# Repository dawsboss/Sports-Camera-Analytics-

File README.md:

# Sideline

A pipeline that turns match footage into per-player data a coach can use.
It is built for a fixed camera that sees the whole pitch; Veo follow-cam
exports are the proof-of-concept input, used because the footage already
exists and because a hostile input keeps the pipeline honest. The two
differ in exactly one stage, registration, and everything else is shared.
The design is in [`docs/SPEC.md`](docs/SPEC.md); read it first.

Published aggregates land in Firebase next to the fixture that
[`soccer-manager`](https://github.com/dawsboss/soccer-manager-) already
tracks. Raw video never leaves the homelab.

## Where this is

| Milestone | State |
| --- | --- |
| M1 registration spike | **Run on two real Veo exports. The classical detector fails the gate on both** after every improvement that could be measured (per-frame grass colour, line thresholds that follow it, plausibility checks compared three ways on four datasets). A pretrained line network, unmodified, already finds on the worn field what the classical code cannot; fine-tuning it on this footage is the next registrar. The measurements are in [`spike/evals/`](spike/evals/) and the plan in [`docs/NEXT.md`](docs/NEXT.md). |
| M2 skeleton | API, Postgres, MinIO, RQ worker, S0 ingest and S1 sampling. Runs with no services on a laptop, or under `docker compose`. |
| M3 detection | Feasibility measured: players are found off the shelf, the ball is not, by any model tried. A ball detector trained on this footage is the gate for possession, passes and restarts. Not built. |
| M4 onward | Not started. |

## Run the M1 spike

```
python -m venv .venv && . .venv/bin/activate
pip install -e ".[dev]"
sideline spike path/to/veo-export.mp4 --frames 200 --out spike/out
```

Then open `spike/out/overlays/` and read the summary. [`spike/README.md`](spike/README.md)
says what the numbers mean, what the overlays show, and what the machinery
cannot do yet. `sideline spike --selftest` runs the same thing on rendered
frames with known truth, which checks the code rather than the footage.

## Run the skeleton

With no services at all, against a directory and SQLite:

```
sideline ingest path/to/match.mp4 --pitch-length 100 --pitch-width 64
ls data/blobs/matches/<id>/
```

With the real stack:

```
docker compose up --build
curl -F file=@match.mp4 -F capture_mode=followcam -F pitch_length=100 -F pitch_width=64 \
     -F kickoff_offset_ms=95000 localhost:8000/matches
```

The API docs are at `localhost:8000/docs`, MinIO's console at `:9001`. The
upload takes the accompanying inputs the spec lists (`sm_match_id`, roster,
stints and periods as JSON, kickoff offset, pitch dimensions), stores the
file under `matches/{id}/source/`, and queues S0 then S1 unless `stages`
names more. Every stage writes `matches/{id}/{stage}/v{n}/` with a
`manifest.json` recording its config and inputs; a re-run is a new version.

Players, the ball and restarts, on a machine with a GPU and the `eval`
extra installed, with no services:

```
sideline ingest match.mp4 --kickoff-offset-ms 83000 \
    --stages s0_ingest,s1_sampling,s2_detection,s3_tracking,s8_events
python spike/evals/restarts_on_taps.py --match-dir data/blobs/matches/<id> --sm matches-node.json
```

The first writes `detections.parquet`, `fragments.parquet` and
`events.parquet` (throw-ins, corners, goal kicks, free kicks, kick-offs,
keeper claims, each with the taker's track), plus `events.csv`, the same
rows as a coach would write them down: match clock, event, who, how sure.
`sideline log <id>` prints that list and `sideline overlay <id>` renders
it onto the frames. The eval script scores the events against the
corners, throw-ins and goal kicks the coach tapped in the minutes app.
`docs/NEXT.md`, "Restarts without registration", says why this needs no
pitch coordinates and what it still needs.

## Review, on your own network

```
sideline serve --data ./data          # the same directory `sideline ingest` wrote
```

Then open `http://<that machine>:8000/review` from any browser on the
same network, phone included. The landing page lists the matches with
where each has got to, and takes new film: a video file, or a direct link
to one that the server fetches (a Veo match page is not the file; the
tagger's README says how to get the direct link). Ingest and sampling run
in the background on the machine serving the page, and the list shows how
far each step has got. A Veo export is H.264 already, so ingest copies its
stream into a fresh MP4 in a minute or two rather than re-encoding it for
an hour; anything else is transcoded. Detection needs the model and a GPU,
so by default it is left for the GPU machine:

```
rsync -a sideline@<homelab>:/srv/sideline/data/ ./data/      # bring the match over
sideline run <match id> --data ./data                        # detection, tracking, restarts
rsync -a ./data/blobs/ sideline@<homelab>:/srv/sideline/data/blobs/   # send the artifacts back
```

Tick "also find the players, the ball and the restarts here" to run it
all on the serving machine instead, when that machine has the model.

A match opens into the review. The page plays the match at each
event the pipeline wrote, draws the taker, the ball and every tracked
box, and takes one of four taps: right; what it was instead, one
button or digit per kind; wrong taker, by tapping the right player; not
an event. The clip runs from four seconds before the release to eight
after, and `[` and `]` add five seconds at either end. With a roster uploaded it also
names the taker. The chips above the list narrow it to one kind of
event (every throw-in, every unnamed restart), and `j`/`k` and the tap
that follows a verdict then stay within that kind. After a re-run of
the events the verdicts given on the earlier version are shown on the
new one, dashed, wherever the same moment is still an event; they stay
rows of the version they were given on. Each tap is a row in the database (`event_decisions`,
`review_decisions`), never an edit to an artifact, and
`GET /matches/<id>/review/decisions` exports them. The frames the page
shows are most of the footage at 5 fps and are served by this API to
browsers on this network and nowhere else: keep the API on the LAN or a
Tailscale network, never on the open internet and never behind a public
tunnel (the spec's Cloudflare Tunnel option does not apply to this API).
There is no login. The compose stack serves the same page at
`:8000/review`.

### On the homelab, as a service

On a Debian or Ubuntu machine (a Proxmox LXC or VM), as root:

```
curl -fsSL https://raw.githubusercontent.com/dawsboss/Sports-Camera-Analytics-/main/deploy/install-homelab.sh | bash
```

or clone the repository and run `deploy/install-homelab.sh`. It makes a
`sideline` user, a checkout and a virtualenv under `/srv/sideline`, and a
systemd service (`deploy/sideline.service`) that serves the API and the
review page on port 8000 of every interface, from boot, with uploads
running on a background thread of the service. Run it again to update.
Matches live in `/srv/sideline/data`, the layout `sideline ingest --data`
writes, so a match can also be processed whole on the GPU machine and
copied in:

```
rsync -a --delete ./data/ sideline@<homelab>:/srv/sideline/data/
```

Review on the homelab's copy from then on; the verdicts are rows in its
database. `SIDELINE_BRANCH=<branch>` before the script installs a branch
instead of `main`.

### The GPU worker

With a GPU in the container, the same machine does the detection too and
the gaming PC drops out of the loop. Run the installer with
`SIDELINE_GPU=1`. It installs torch from the CUDA 12.6 wheels (the last to
support a Pascal card such as a GTX 1080; set `SIDELINE_TORCH_INDEX` for a
newer card), the detector, and a second service, `sideline-worker`, which
polls the database for queued jobs and runs them in its own process while
the API only queues them. The worker holds the detector and the GPU; the
API stays light. Tick "also find the players, the ball and the restarts
here" when adding film, and the list shows detection running frame by
frame.

The container needs the card first. Share it at the host rather than
passing it through: install the NVIDIA driver on the Proxmox host, then hand
the devices to the container (`/dev/nvidia0`, `/dev/nvidiactl`,
`/dev/nvidia-uvm`, `/dev/nvidia-uvm-tools`, `/dev/nvidia-modeset` as
present, as `dev0:`.. entries on the container, or the older
`lxc.cgroup2.devices.allow` and `lxc.mount.entry` lines) and install the
same driver version's user-space libraries inside it. Any other container
can mount the same devices and share the card; the driver time-slices it,
and the eight gigabytes of memory are what they contend for. If another
project needs the card by day, a systemd timer that starts
`sideline-worker` at night is the whole scheduling policy.

## Layout

```
sideline/
  contracts.py        tracks/events/registration Parquet schemas, match.json, player_stats.json
  timeline.py         video time <-> match seconds, and the minutes app's taps, via soccer-manager's nodes
  sports/             the plugin boundary; soccer.py is the pitch model, entities, stat definitions, restart rules
  detection.py        S2's detector behind a protocol: an Ultralytics checkpoint, or a script for tests
  tracking.py         S3's tracker: people by overlap or centre, the ball by where it went, no dependencies
  events.py           dead balls from fragments: still, then struck or thrown, and who took it, in player heights
  possession.py       who has the ball in each sample: feet or hands within a touch, spells that survive a missed sample
  registration/       S5: one interface, two implementations
    followcam.py        per-frame fit from painted lines (the PoC)
    static.py           clicked landmarks once per placement, homography or spline (the product)
    lines.py            grass, paint, line segments
    synthetic.py        frames rendered through a known camera, for tests and the selftest
  storage/            blob store (local or MinIO) and the versioned artifact layout
  db/                 matches, jobs, stage runs, review decisions
  stages/             s0_ingest, s1_sampling, s2_detection, s3_tracking, s8_events
  overlay.py          the sampled frames with tracks, the ball's path and each event's call, as an MP4
  api/                FastAPI: uploads, artifacts, and the review page's routes
  worker/             RQ worker
  spike.py, cli.py    the M1 spike and the `sideline` command
deploy/               install-homelab.sh and sideline.service: the API as a LAN service on the homelab
docs/SPEC.md          the design, copied from the living doc
web/                  the tagger (GitHub Pages) and review.html (served by the API on your network)
hardware/             the static rig (M9): what to buy, the printed four-camera head or hidden pod, aim cards
tests/                pytest; everything runs on a CPU with no services
```

## Tests

```
pytest
```

Registration is checked against frames rendered through a known camera:
box views must land within a metre of the truth, a midfield view with one
crossing line must be refused with a reason, and a sweep of views must
register at least 70% with few confident wrong answers. The stages, the
API and the local pipeline run on a three-second synthetic clip. None of
that is the M1 gate; the gate is real footage.

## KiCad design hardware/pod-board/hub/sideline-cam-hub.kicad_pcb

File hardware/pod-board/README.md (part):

# The pod board: our own cameras instead of the IP domes

Four small Sony IMX678 camera heads in one sealed pod. An RK3588
module in the pod records all four 4K streams to an SSD, and one PoE++
cable runs down the mast. It replaces the IP cameras that the Sideline
Rig Brief (the rig's design doc of 25 September 2026) picks in Part 1,
two Reolink RLC-843A domes and two RLC-820A turrets, and shrinks the
brief's Part 3 pod around them. Against the rigs in `../README.md`, it
replaces the cameras, the switch and the recorder.

It is built from one open-hardware carrier and one new board:

- **The carrier** is [Antmicro's Jetson Orin
  Baseboard](https://github.com/antmicro/jetson-orin-baseboard). It is
  built as it is, with one resistor array moved, and it carries a
  [Mixtile Core 3588E](https://www.mixtile.com/core-3588e/) (RK3588).
- **The camera hub** (`hub/`) is the new PCB. It turns the baseboard's
  two 50-pin camera connectors into four Raspberry Pi 5 style camera
  ports. It adds a power switch per camera, a frame-sync bus that makes
  one camera the master, an IMU that samples on the frame pulse and a
  humidity sensor.

**State:** designed and checked in KiCad, and nothing bought, built or
filmed. The hub's schematic passes ERC, and its board passes DRC and
the schematic-parity check (see "The camera hub"). Every figure below
is either sourced or marked as an estimate.

## Why build it: smaller, lighter, and our settings

| | Recommended IP set (brief, Part 1) | Pod board |
| --- | --- | --- |
| Cameras on the mast | 2.44 kg | about 0.1 kg: four heads with lenses (estimate) |
| Whole rig on the mast | about 4.4 kg of a 4.5 kg rating | about 0.9 kg (estimate, see "Power, data, heat and weight") |
| Pod | about 300 x 240 x 300 mm (design v2) | about 160 x 140 x 120 mm (estimate; not drawn yet) |
| Bitrate per camera | 8 Mbps, the camera's maximum | our choice; plan 35 Mbps, test 20 to 50 |
| Shutter | "manual", fastest step not published | set in the sensor: 1/1000 s |
| White balance | whatever the firmware allows | fixed ISP gains for the match |
| Lens | motorized zoom that must return after power-up | fixed M12 lenses, focus locked |
| Frame sync | none | one XVS/XHS pulse drives all four sensors |
| Mast tilt | not measured | an IMU sample tagged to every frame |
| Smallest ball, 11v11 | 9.2 px | 8.0 px (middle of the near goal line) |
| Ball at the far corner | 9.7 px | 10.1 px |
| Cost of the first unit | $500 | roughly $1,300 to $2,200 (estimate, see "What to buy") |

The bitrate decides it, as the brief says. An 8 Mbps stream is the
first thing to smear a 9 px ball; here it is a setting.

## What it sees

`rig_geometry.py --head homebrew-678` models the heads: IMX678 at
3840 x 2160, with Commonlands M12 lenses modelled rectilinear. The
lens angles are Commonlands' own figures for each lens on the IMX678.
The rig is an 8 m mast, 10 m behind the touchline, at halfway:

| | 11v11 (100 x 64 m) | 9v9 (69 x 46 m) | 7v7 (55 x 37 m) |
| --- | --- | --- | --- |
| Smallest ball anywhere | 8.0 px | 10.4 px | 12.7 px |
| Ball at the far corner | 10.1 px | 12.6 px | 15.2 px |
| Smallest player | 61 px | 70 px | 85 px |
| Worst foot position | 0.25 m per px | 0.13 | 0.09 |
| Pitch + 2 m in frame, feet and heads | 100% | 100% | 100% |
| Trials with a gap inside the lines, every camera up to 2 degrees off | 0 of 300 | 0 of 300 | 0 of 300 |

| Camera | Lens | Horizontal angle on IMX678 | Yaw, L / R | Tilt down |
| --- | --- | --- | --- | --- |
| FAR-L, FAR-R | [Commonlands CIL083](https://commonlands.com/products/low-distortion-8mm-m12-lenses), 8.0 mm f/2.8, -0.5% TV distortion | 51 degrees | -24 / +24 | 4 |
| NEAR-L, NEAR-R | [Commonlands CIL042](https://commonlands.com/products/no-distortion-4mm-m12-lens-cil042), 4.2 mm f/2.6, -0.7% TV distortion | 85 degrees | -40 / +40 | 29 |

Aim cards and coverage maps for all three pitches are in `aim/`.

- **Why these aims.** A wider far pair (around 32 degrees of yaw) gets
  the smallest ball up to 9.3 px. But it leaves the middle of the far
  touchline to the near cameras' top edge, and 7 to 27% of the 2-degree
  trials then lose it. The far pair turns in to overlap there instead.
- **Where it gives up to the Reolinks.** Only the middle of each goal
  line, near side, falls below 9 px: 0.9% of the pitch. The Reolinks'
  near lens is a barrel-distorted security lens, which puts more pixels
  in the middle of the frame than a low-distortion one. A barrel M12
  lens of about 86 degrees would close the gap, but none with a
  published IMX678 angle turned up.
- **What was tried.** Nothing in Commonlands' IMX678 list sits at the
  brief's 56 degrees. The 6.2 mm CIL062 (64 degrees) gives 7.9 px;
  8.0 px is the best of the real lens pairs tried.

## What to buy

Prices were checked on 26 September 2026 where a source is linked, and
the rest are estimates marked "about". Check before ordering.

### Compute and carrier

| Qty | Item | Price | Notes |
| --- | --- | --- | --- |
| 1 | [Antmicro Jetson Orin Baseboard](https://order.openhardware.antmicro.com/), rev 1.3.4 | $499, out of stock at CircuitHub | Or build it from the open files; see "Baseboard setup" for the one change |
| 1 | [Mixtile Core 3588E](https://www.mixtile.com/store/som/core-3588e/), RK3588, 16 GB / 128 GB | between $132 (4 GB / 32 GB) and $338 (32 GB / 256 GB) | Jetson SO-DIMM module on 5 V; the 4 GB version should record, 16 GB leaves room |
| 1 | NVMe SSD, M.2 key M, 1 TB | about $80-150 | Recording; the baseboard's M.2 slot |
| 1 each | A second baseboard, module and SSD (fallback only) | see "If one module is not enough" | Only if the bench test fails; the hub splits between two boards as built |

### Camera heads

| Qty | Item | Price | Notes |
| --- | --- | --- | --- |
| 4 | IMX678 camera board with a Raspberry Pi 22-pin connector and an M12 mount, e.g. [Soho Enterprise SE-SB03-IMX678](https://forums.raspberrypi.com/viewtopic.php?t=306964&start=50) | on request | It must bring out XVS and XHS for sync. Soho's boards sync "by XVS"; confirm XHS before ordering |
| 2 | [Commonlands CIL083](https://commonlands.com/products/low-distortion-8mm-m12-lenses), 650 nm IR-cut | $19 each | Far pair |
| 2 | [Commonlands CIL042](https://commonlands.com/products/no-distortion-4mm-m12-lens-cil042), F/2.6, 650 nm IR-cut | $49 each | Near pair; the F/2.6 version resolves 8 MP at 2 um |

[StarlightEye](https://github.com/will127534/StarlightEye) (IMX585,
C-mount) is the open-source alternative. It has twice the pixel area
for dull days, and brings XVS and XHS out on U.FL. It also needs
C-mount lenses of about 12 mm and 6 mm, which weigh several times the
M12s. The hub serves either.

### The hub and cables

| Qty | Item | Price | Notes |
| --- | --- | --- | --- |
| 1 | Camera hub, this board, 4 layers, assembled one side | about $30-50 each in fives (estimate) | `hub/fab/` has the Gerbers, drill, BOM and placement files |
| 2 | 50-pin 0.5 mm FFC, 100-150 mm | a few dollars | Baseboard J7 to hub J1, J8 to J2; pin N to pin N (see "Cables") |
| 4 | 22-pin 0.5 mm FFC (Raspberry Pi 5 camera cable), 150-200 mm | about $3-5 each | Hub P1-P4 to the heads |
| 4 | JST SH 4-pin leads, 150 mm | about $1 each | Sync, hub J4-J7 to each head's XVS/XHS |

### Base station changes (fixed install on PoE only)

A battery pod needs no base case. This is for a pod on PoE.

| Qty | Item | Notes |
| --- | --- | --- |
| 1 | IEEE 802.3bt PoE++ injector, 60 W, e.g. [TP-Link TL-POE170S](https://www.omadanetworks.com/us/business-networking/omada-accessory-poe-adapter/poe170s/), about $50 | Replaces the USW-Flex and the POE-50-60W injector. The baseboard's PD is 802.3bt (TPS2372-3) |

The travel router, mini PC, power station, mast, guys and Cat6 run are
unchanged from `../README.md`. The four camera patch cables and the
switch go, and the mini PC now only previews, serves time and takes
the offload.

### Battery parts (to price once the power board is designed)

| Qty | Item | Notes |
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
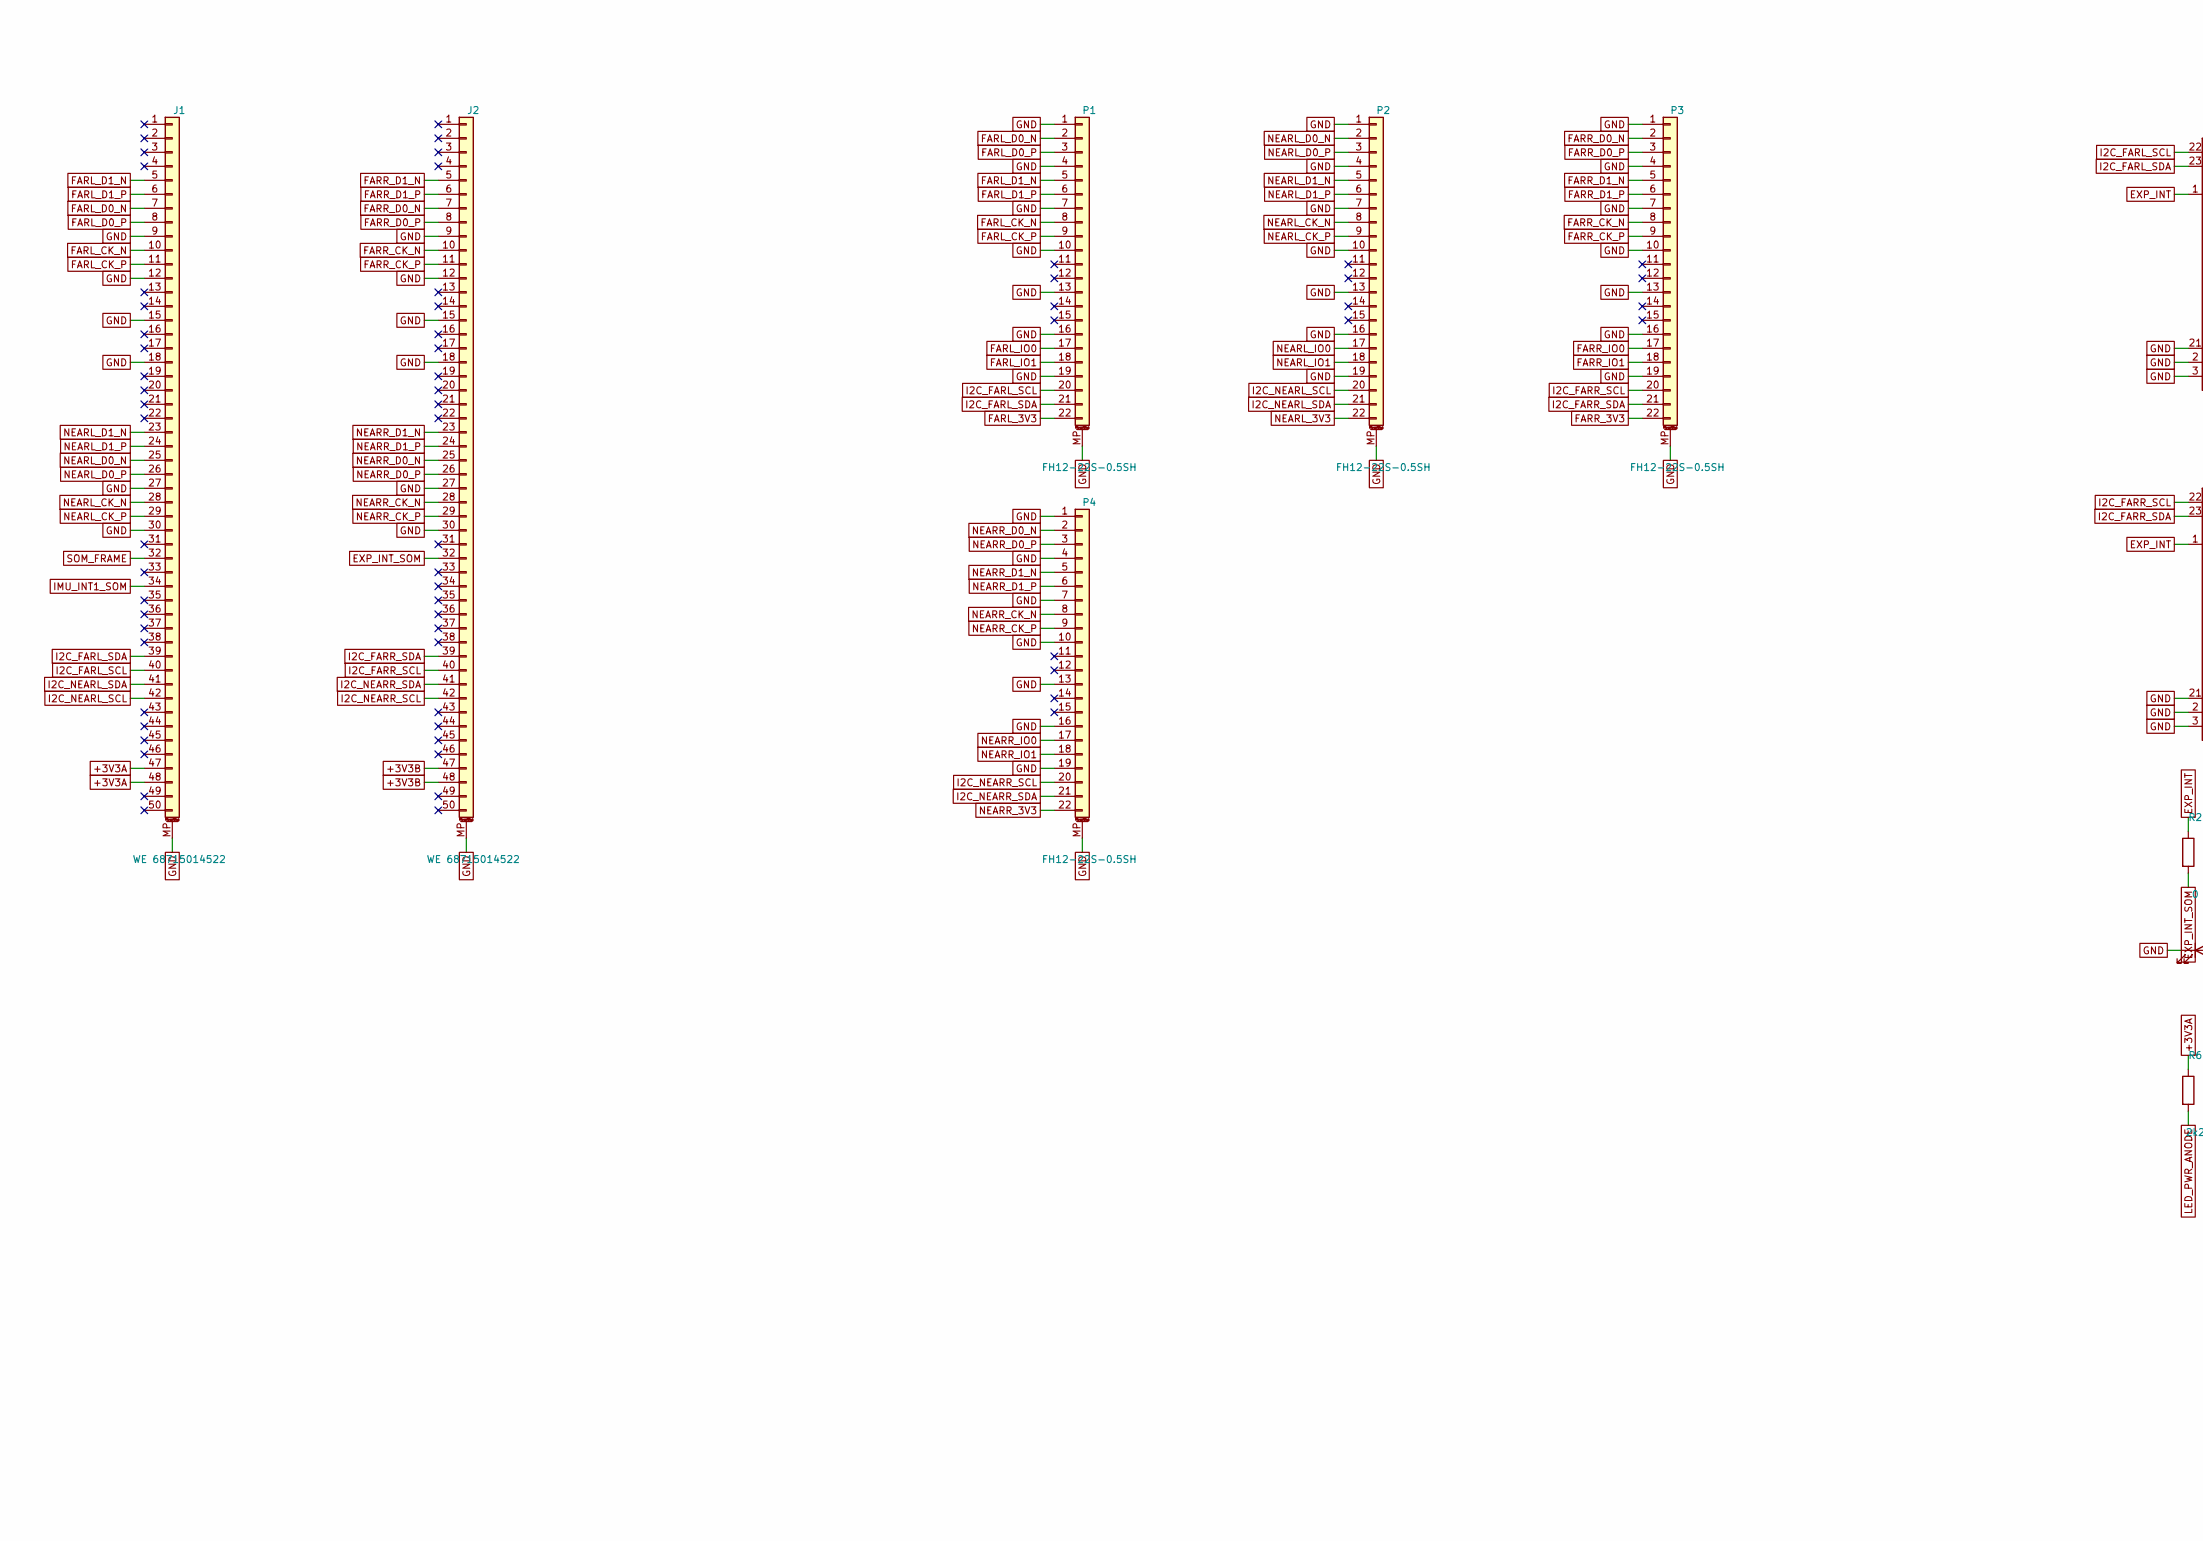
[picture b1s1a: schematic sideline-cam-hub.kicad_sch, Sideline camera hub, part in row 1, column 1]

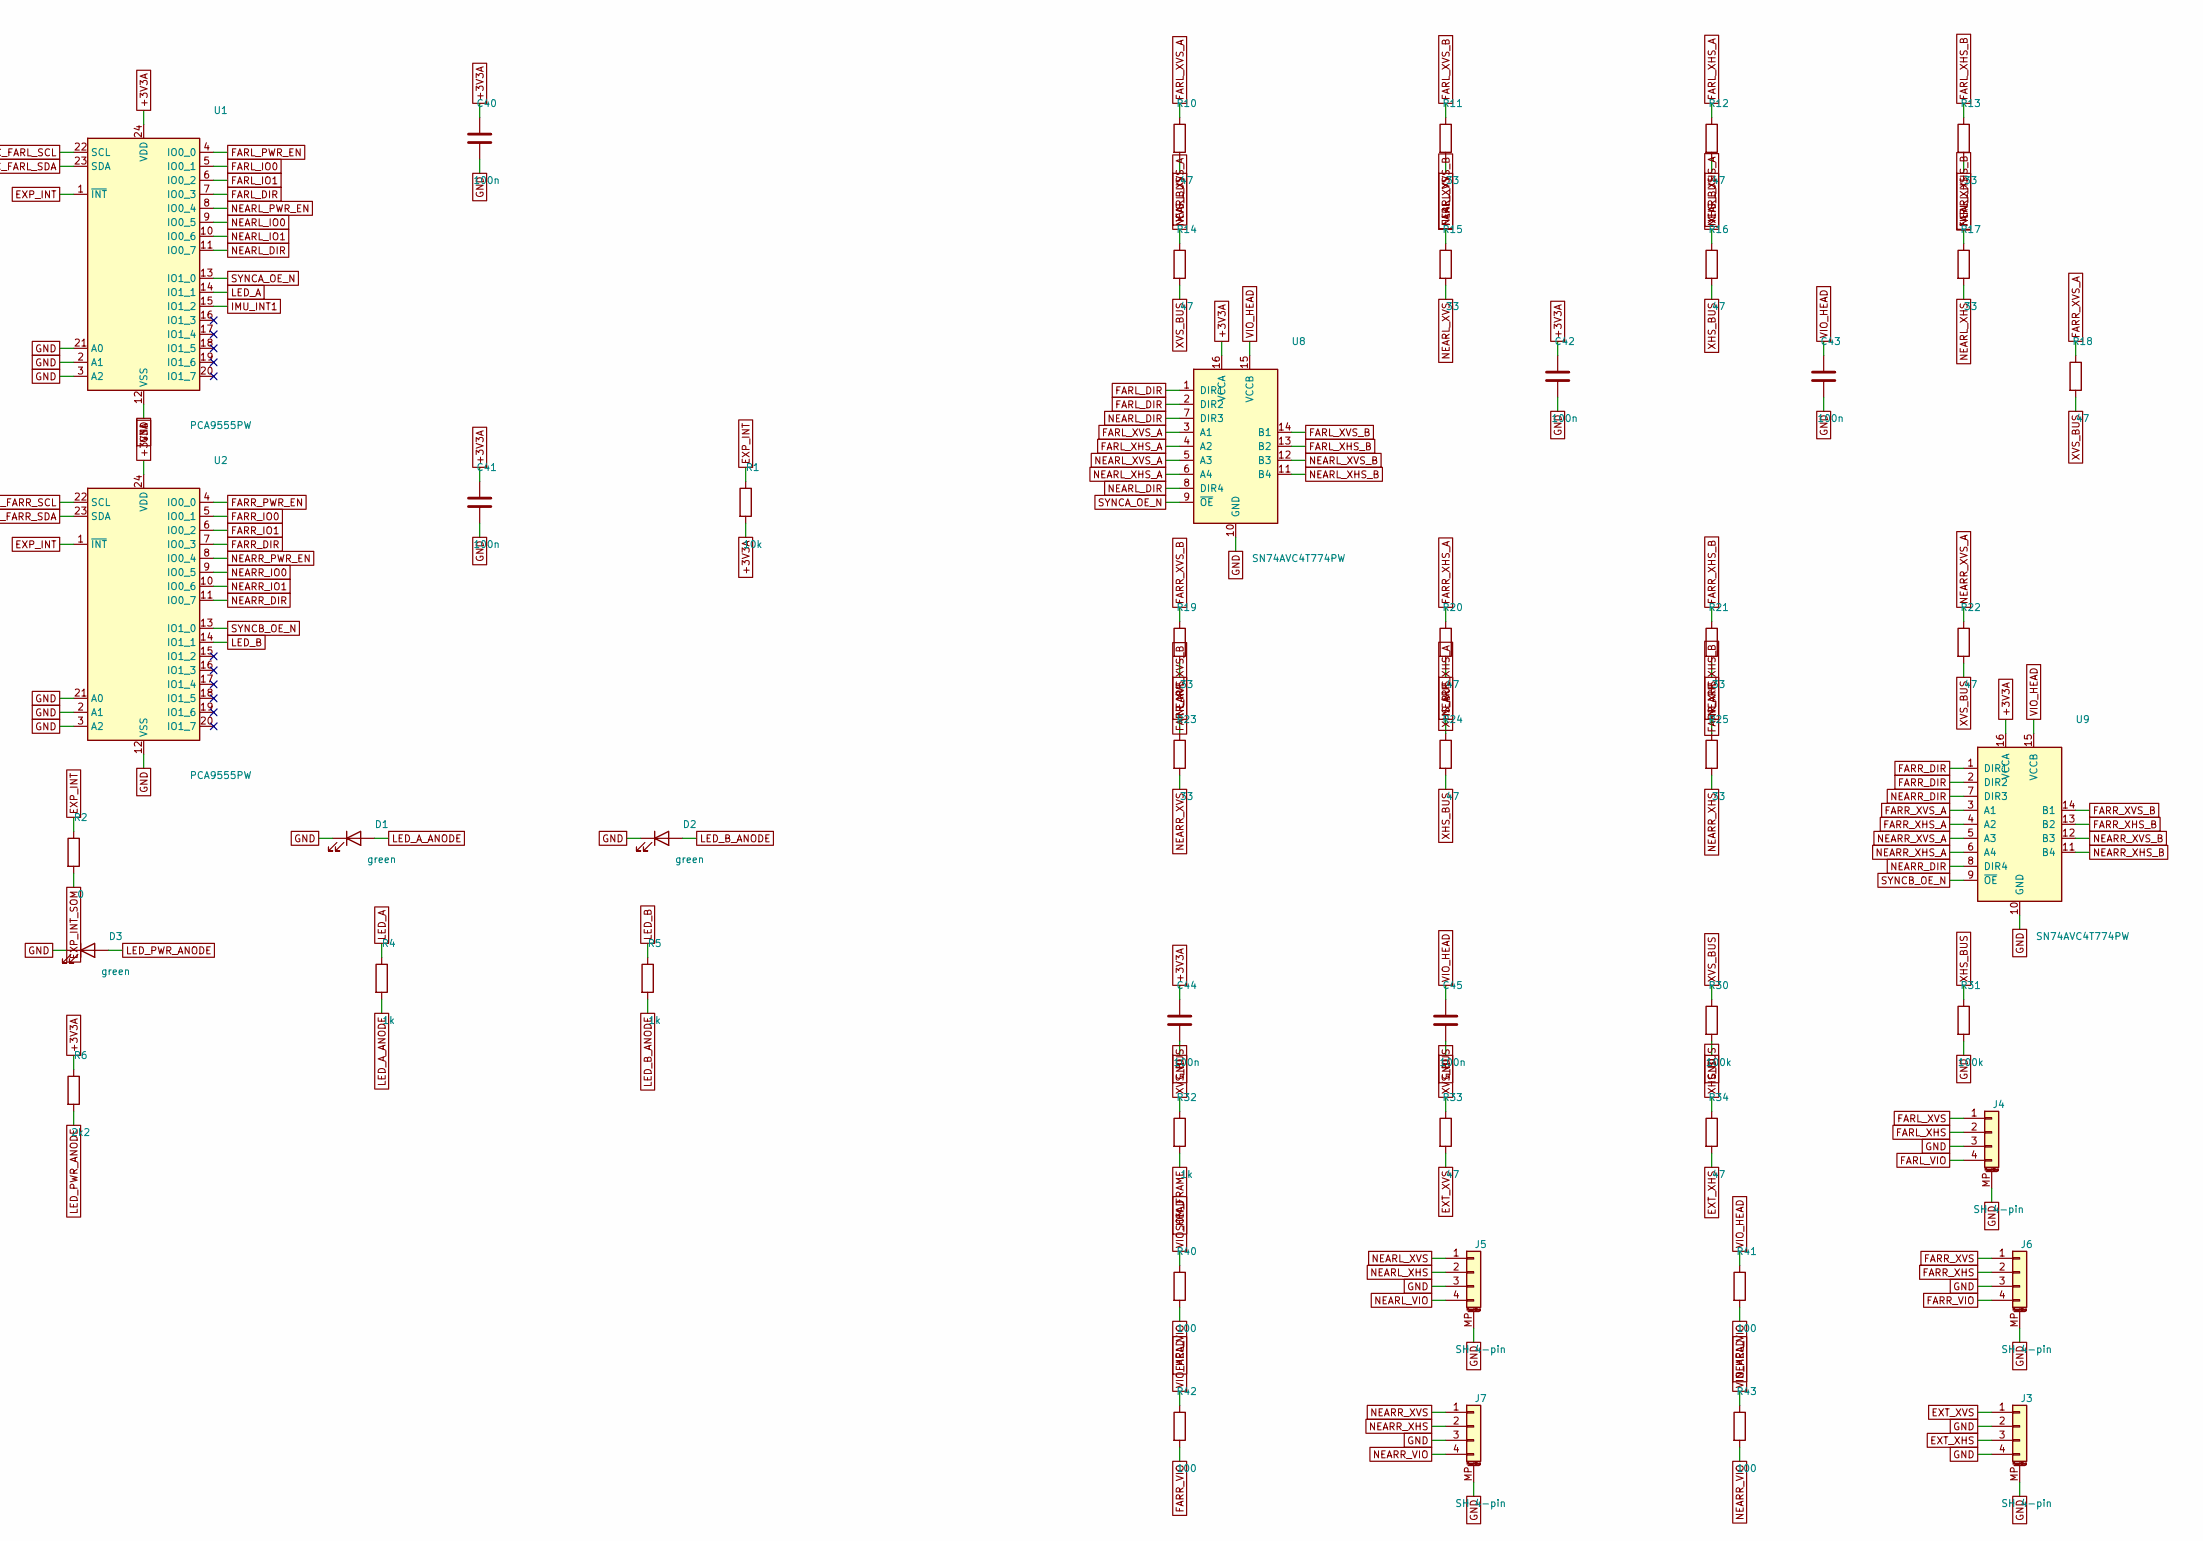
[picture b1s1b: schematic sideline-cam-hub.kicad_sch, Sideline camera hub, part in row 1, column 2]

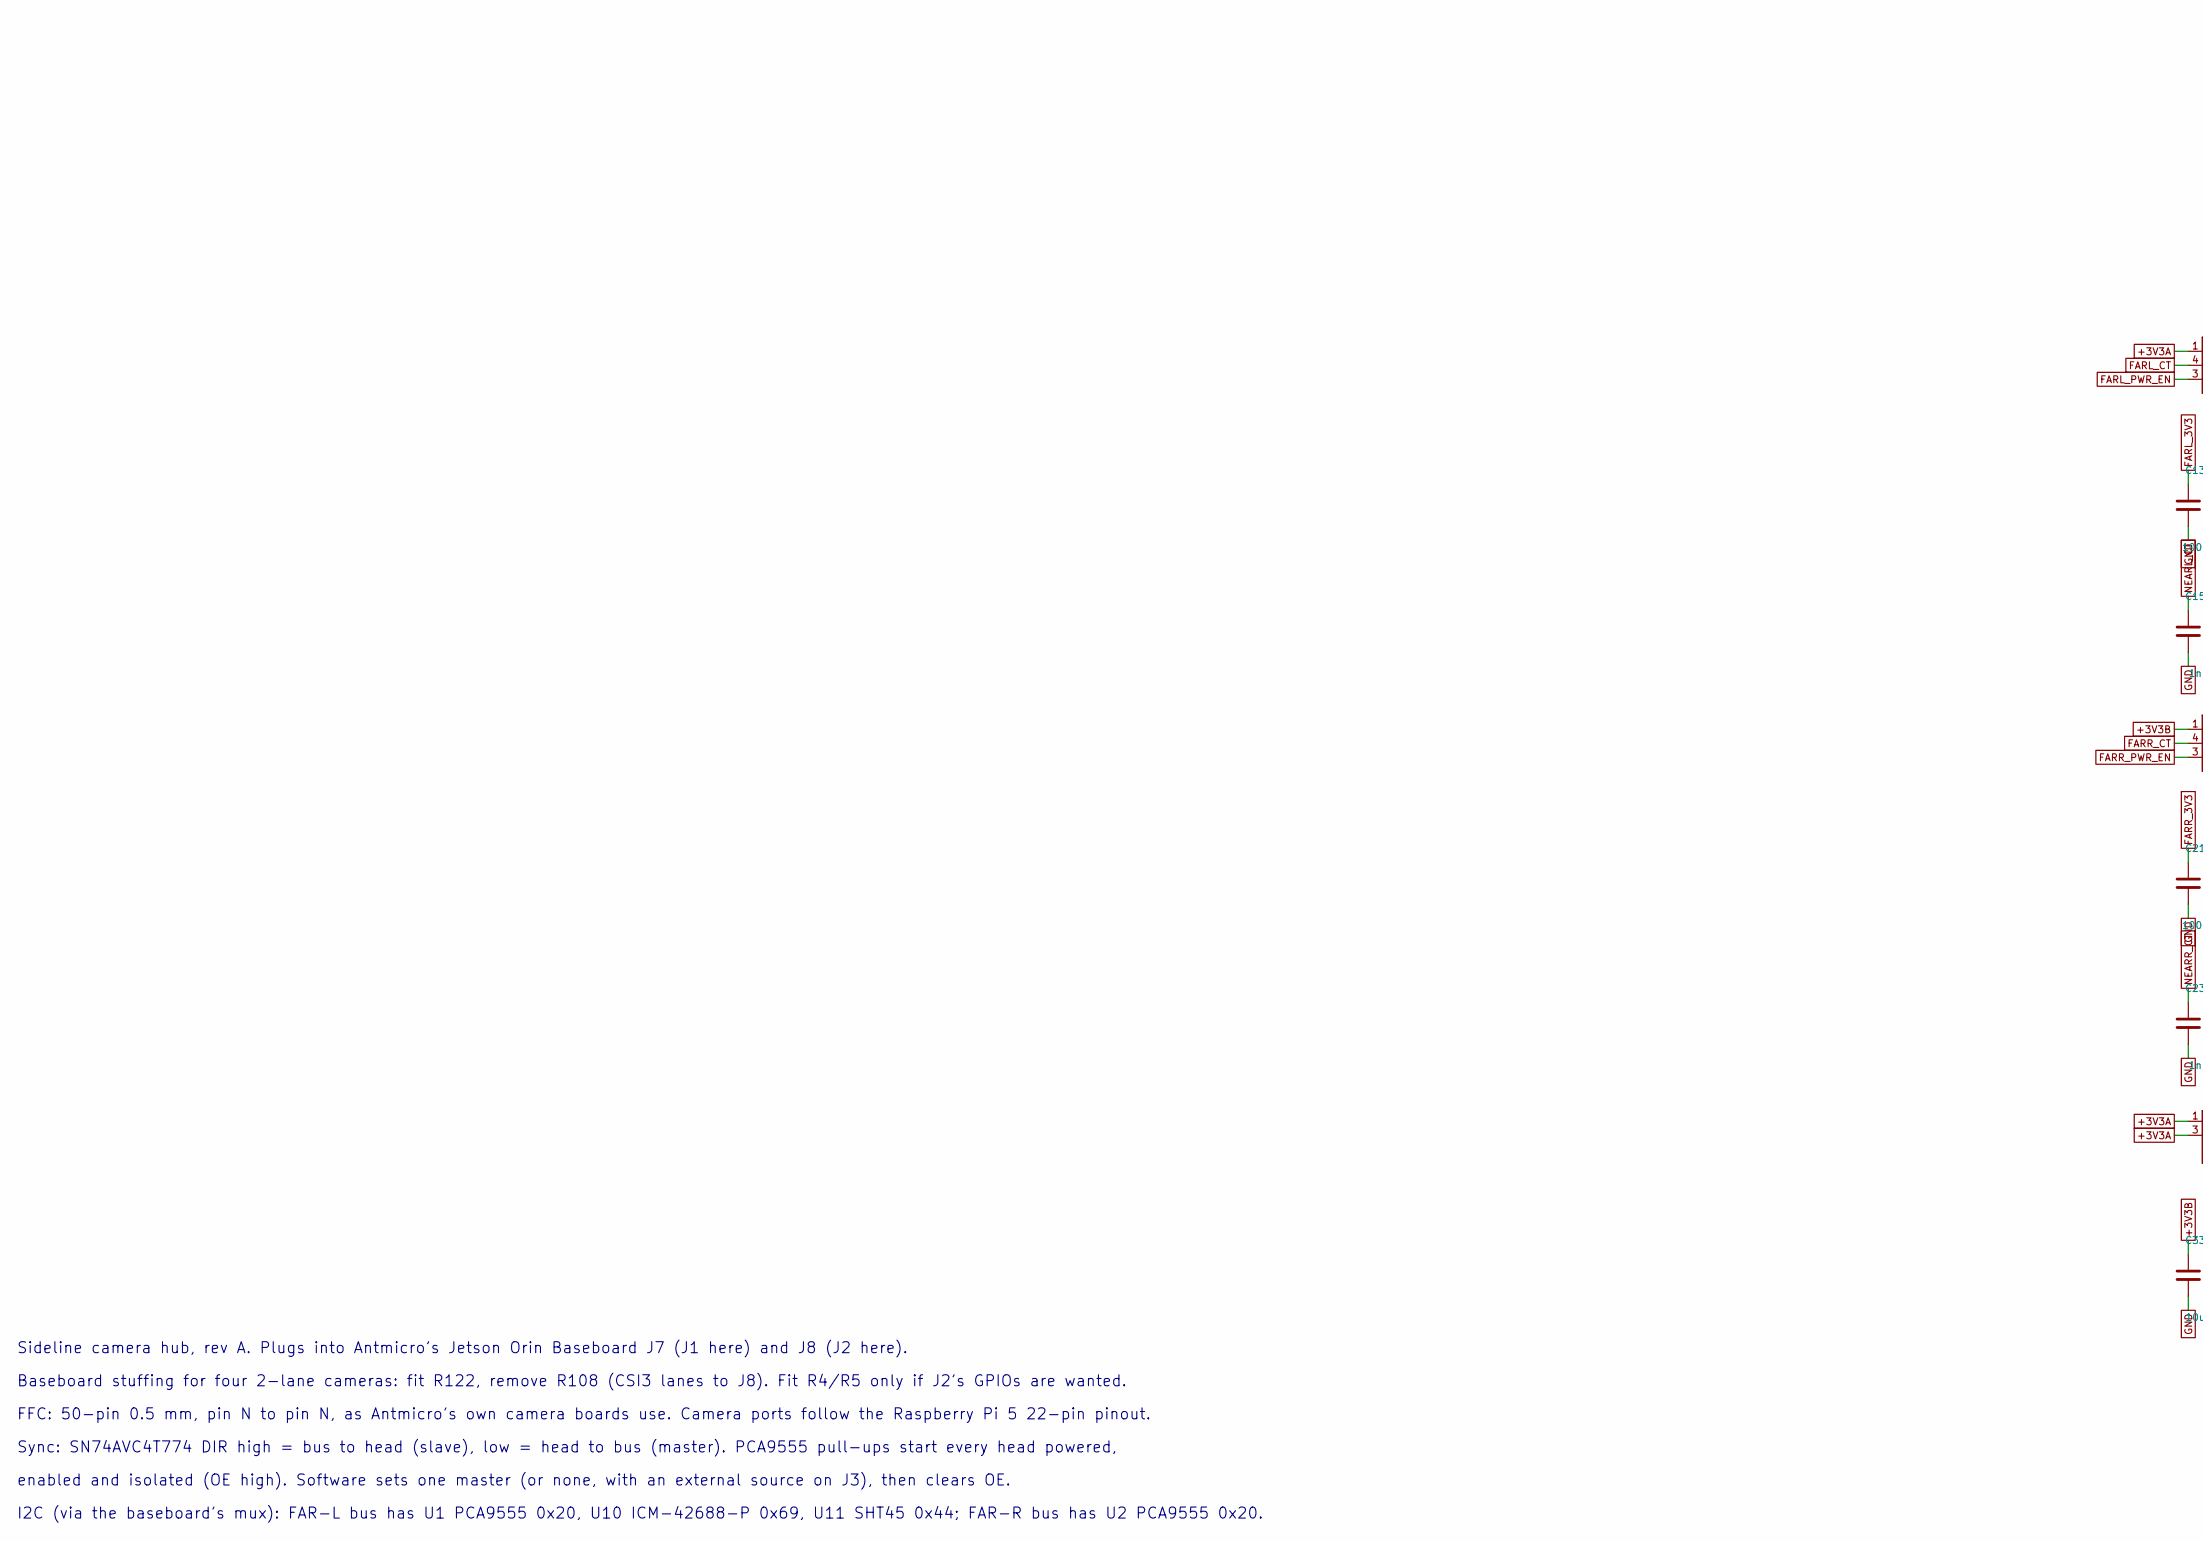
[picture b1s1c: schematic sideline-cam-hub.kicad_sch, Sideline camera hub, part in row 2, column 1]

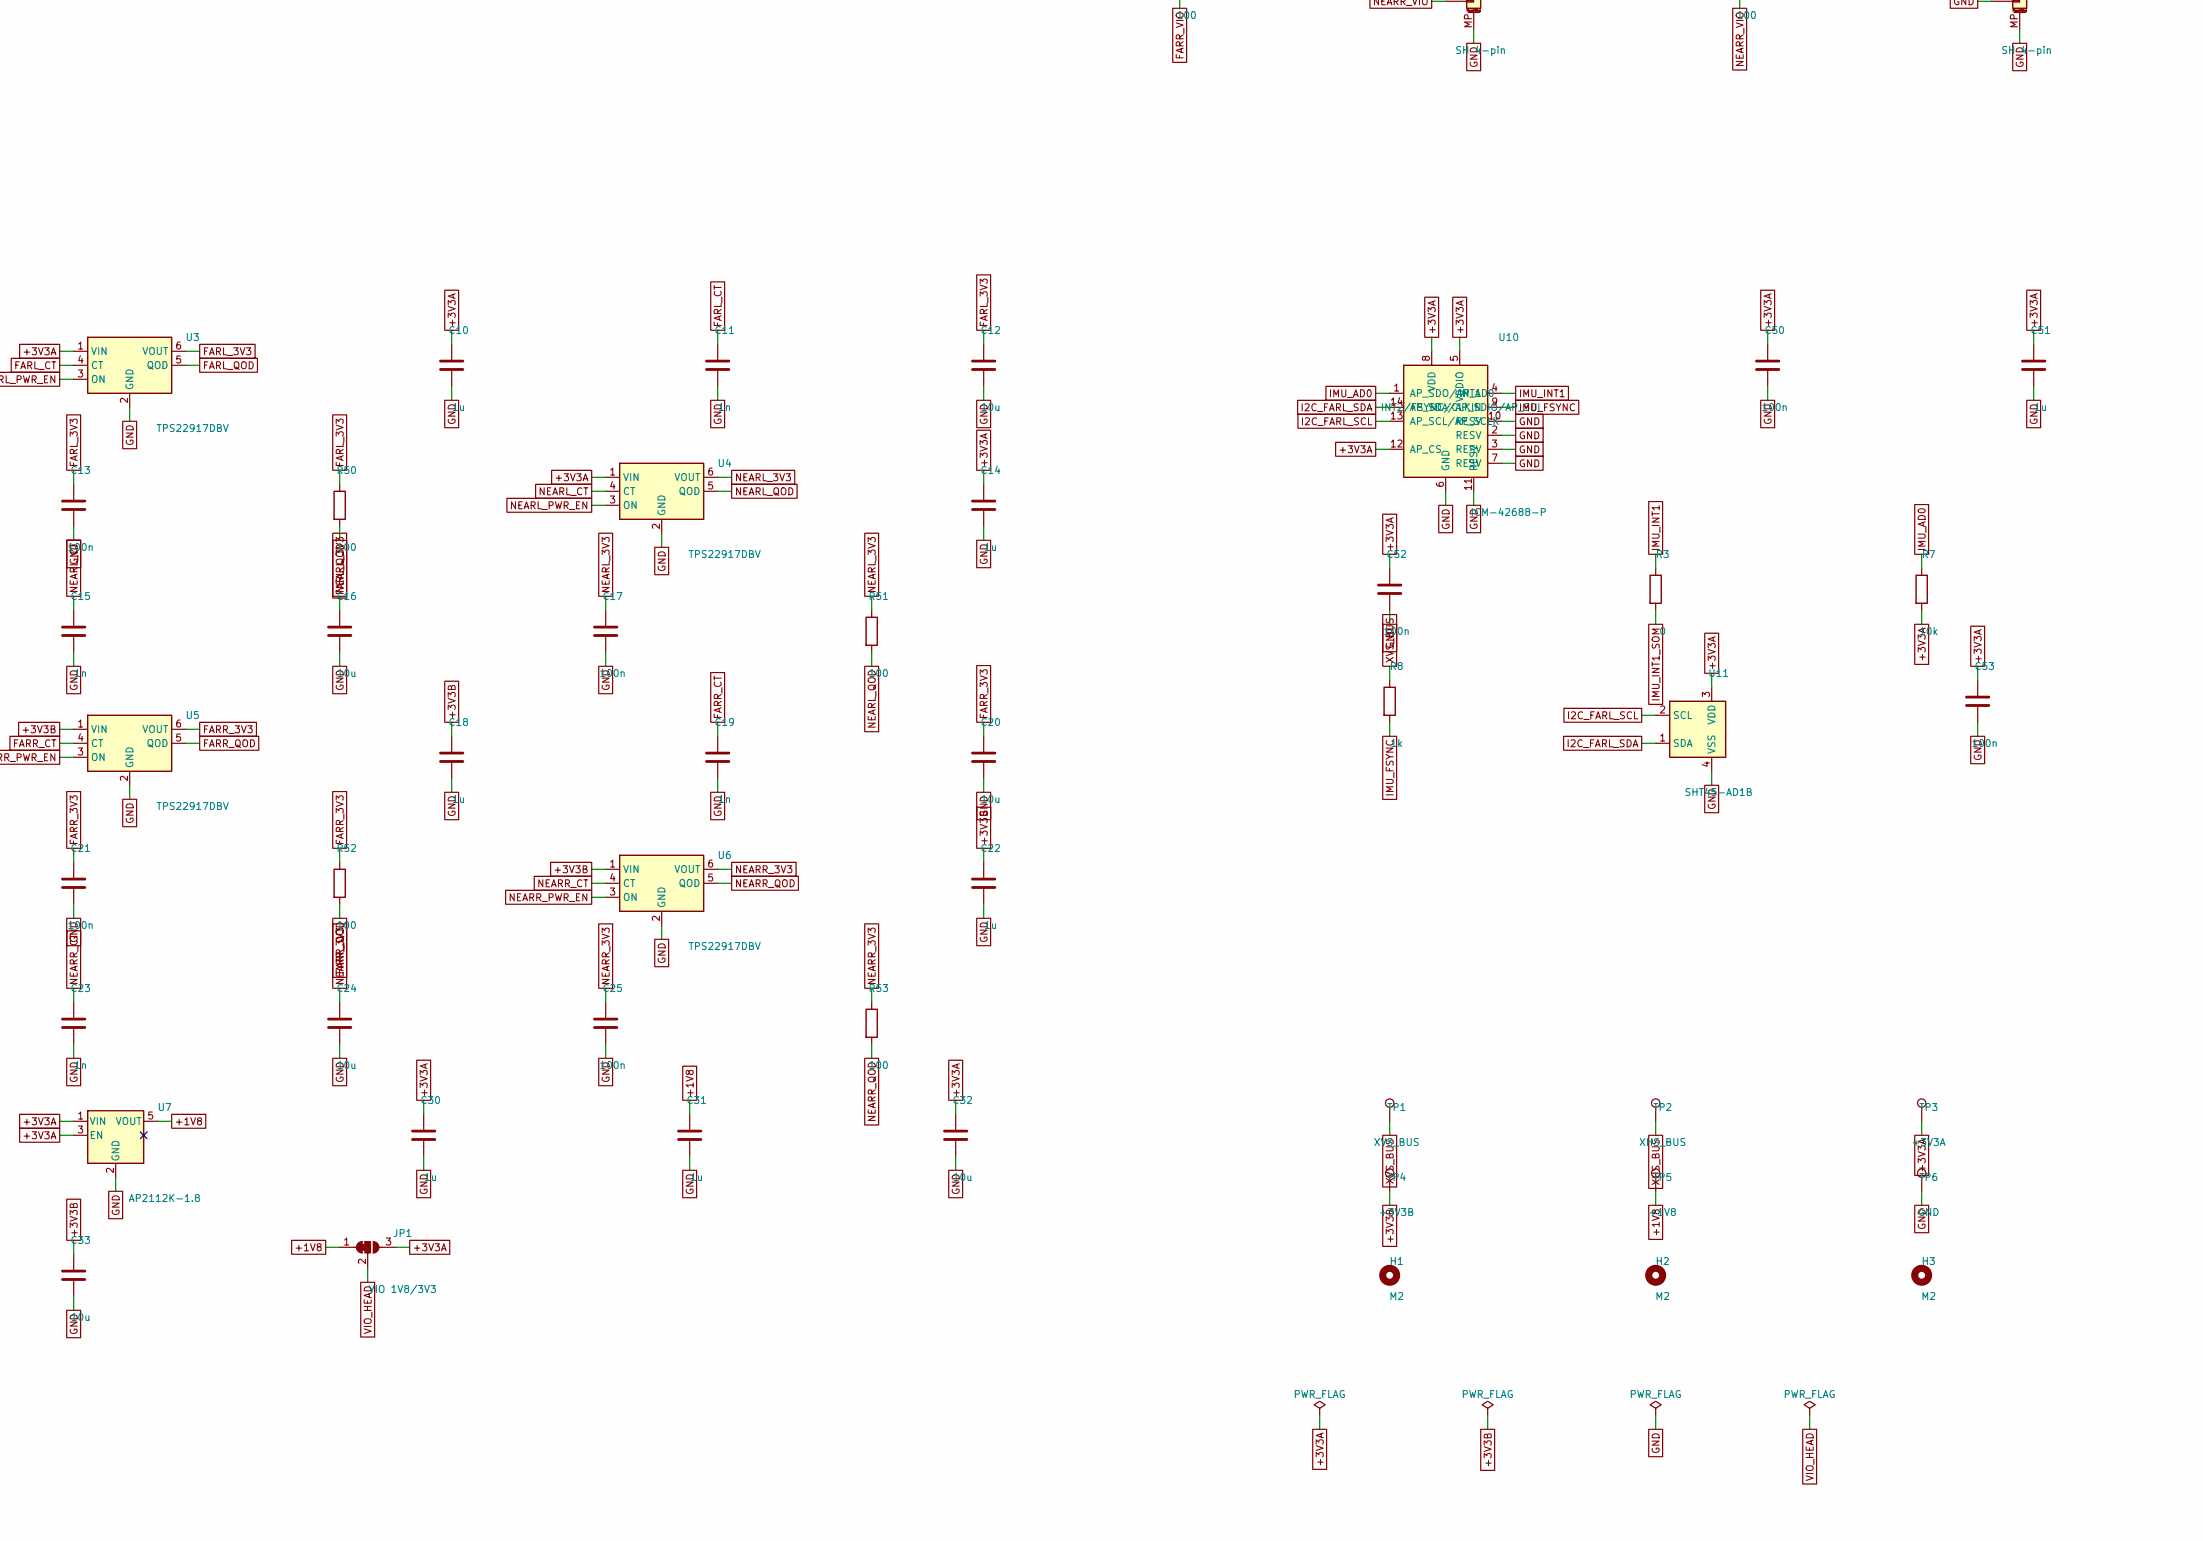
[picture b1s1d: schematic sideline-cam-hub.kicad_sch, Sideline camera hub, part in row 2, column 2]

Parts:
C10, C14, C18, C22, C30, C31, C51: 1u; C_0402_1005Metric
C11, C15, C19, C23: 1n; C_0402_1005Metric
C12, C16, C20, C24, C32, C33: 10u; C_0603_1608Metric
C13, C17, C21, C25, C40, C41, C42, C43, C44, C45, C50, C52, C53: 100n; C_0402_1005Metric
D1, D2, D3: green; LED_0603_1608Metric; MPN APT1608SGC
H1, H2, H3: M2; MountingHole_2.2mm_M2
J1, J2: WE 68715014522; WE_68715014522; MPN 68715014522
J3, J4, J5, J6, J7: SH 4-pin; JST_SH_SM04B-SRSS-TB_1x04-1MP_P1.00mm_Horizontal; MPN SM04B-SRSS-TB(LF)(SN)
JP1: VIO 1V8/3V3; SolderJumper-3_P1.3mm_Bridged12_RoundedPad1.0x1.5mm
P1, P2, P3, P4: FH12-22S-0.5SH; Hirose_FH12-22S-0.5SH_1x22-1MP_P0.50mm_Horizontal; MPN FH12-22S-0.5SH(55)
R1, R7: 10k; R_0402_1005Metric
R2, R3: 0; R_0402_1005Metric
R4, R5, R8, R32: 1k; R_0402_1005Metric
R6: 2k2; R_0402_1005Metric
R10, R12, R14, R16, R18, R20, R22, R24, R33, R34: 47; R_0402_1005Metric
R11, R13, R15, R17, R19, R21, R23, R25: 33; R_0402_1005Metric
R30, R31: 100k; R_0402_1005Metric
R40, R41, R42, R43, R50, R51, R52, R53: 100; R_0402_1005Metric
TP1: XVS_BUS; TestPoint_Pad_D1.0mm
TP2: XHS_BUS; TestPoint_Pad_D1.0mm
TP3: +3V3A; TestPoint_Pad_D1.0mm
TP4: +3V3B; TestPoint_Pad_D1.0mm
TP5: +1V8; TestPoint_Pad_D1.0mm
TP6: GND; TestPoint_Pad_D1.0mm
U1, U2: PCA9555PW; TSSOP-24_4.4x7.8mm_P0.65mm; MPN PCA9555PW,118
U3, U4, U5, U6: TPS22917DBV; SOT-23-6; MPN TPS22917DBVR
U7: AP2112K-1.8; SOT-23-5; MPN AP2112K-1.8TRG1
U8, U9: SN74AVC4T774PW; TSSOP-16_4.4x5mm_P0.65mm; MPN SN74AVC4T774PWR
U10: ICM-42688-P; LGA-14_3x2.5mm_P0.5mm_LayoutBorder3x4y; MPN ICM-42688-P
U11: SHT45-AD1B; Sensirion_DFN-4_1.5x1.5mm_P0.8mm_SHT4x_NoCentralPad; MPN SHT45-AD1B-R2

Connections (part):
+1V8: C31.1, JP1.1 (A), TP5.1, U7.5 (VOUT)
+3V3A: C10.1, C14.1, C30.1, C32.1, C40.1, C41.1, C42.1, C44.1, C50.1, C51.1, C52.1, C53.1, J1.47, J1.48, JP1.3 (B), R1.2, R6.1, R7.2, TP3.1, U1.24 (VDD), U2.24 (VDD), U3.1 (VIN), U4.1 (VIN), U7.1 (VIN), U7.3 (EN), U8.16 (VCCA), U9.16 (VCCA), U10.5 (VDDIO), U10.8 (VDD), U10.12 (AP_CS), U11.3 (VDD)
+3V3B: C18.1, C22.1, C33.1, J2.47, J2.48, TP4.1, U5.1 (VIN), U6.1 (VIN)
EXP_INT: R1.1, R2.1, U1.1 (~INT), U2.1 (~INT)
EXP_INT_SOM: J2.32, R2.2
EXT_XHS: J3.3, R34.2
EXT_XVS: J3.1, R33.2
FARL_3V3: C12.1, C13.1, P1.22, R50.1, U3.6 (VOUT)
FARL_CK_N: J1.10, P1.8
FARL_CK_P: J1.11, P1.9
FARL_CT: C11.1, U3.4 (CT)
FARL_D0_N: J1.7, P1.2
FARL_D0_P: J1.8, P1.3
FARL_D1_N: J1.5, P1.5
FARL_D1_P: J1.6, P1.6
FARL_DIR: U1.7 (IO0_3), U8.1 (DIR1), U8.2 (DIR2)
FARL_IO0: P1.17, U1.5 (IO0_1)
FARL_IO1: P1.18, U1.6 (IO0_2)
FARL_PWR_EN: U1.4 (IO0_0), U3.3 (ON)
FARL_QOD: R50.2, U3.5 (QOD)
FARL_VIO: J4.4, R40.2
FARL_XHS: J4.2, R13.2
FARL_XHS_A: R12.1, U8.4 (A2)
FARL_XHS_B: R13.1, U8.13 (B2)
FARL_XVS: J4.1, R11.2
FARL_XVS_A: R10.1, U8.3 (A1)
FARL_XVS_B: R11.1, U8.14 (B1)
FARR_3V3: C20.1, C21.1, P3.22, R52.1, U5.6 (VOUT)
FARR_CK_N: J2.10, P3.8
FARR_CK_P: J2.11, P3.9
FARR_CT: C19.1, U5.4 (CT)
FARR_D0_N: J2.7, P3.2
FARR_D0_P: J2.8, P3.3
FARR_D1_N: J2.5, P3.5
FARR_D1_P: J2.6, P3.6
FARR_DIR: U2.7 (IO0_3), U9.1 (DIR1), U9.2 (DIR2)
FARR_IO0: P3.17, U2.5 (IO0_1)
FARR_IO1: P3.18, U2.6 (IO0_2)
FARR_PWR_EN: U2.4 (IO0_0), U5.3 (ON)
FARR_QOD: R52.2, U5.5 (QOD)
FARR_VIO: J6.4, R42.2
FARR_XHS: J6.2, R21.2
FARR_XHS_A: R20.1, U9.4 (A2)
FARR_XHS_B: R21.1, U9.13 (B2)
FARR_XVS: J6.1, R19.2
FARR_XVS_A: R18.1, U9.3 (A1)
FARR_XVS_B: R19.1, U9.14 (B1)
GND: C10.2, C11.2, C12.2, C13.2, C14.2, C15.2, C16.2, C17.2, C18.2, C19.2, C20.2, C21.2, C22.2, C23.2, C24.2, C25.2, C30.2, C31.2, C32.2, C33.2, C40.2, C41.2, C42.2, C43.2, C44.2, C45.2, C50.2, C51.2, C52.2, C53.2, D1.1 (K), D2.1 (K), D3.1 (K), J1.9, J1.12, J1.15, J1.18, J1.27, J1.30, J1.MP (MountPin), J2.9, J2.12, J2.15, J2.18, J2.27, J2.30, J2.MP (MountPin), J3.2, J3.4, J3.MP (MountPin), J4.3, J4.MP (MountPin), J5.3, J5.MP (MountPin), J6.3, J6.MP (MountPin), J7.3, J7.MP (MountPin), P1.1, P1.4, P1.7, P1.10, P1.13, P1.16, P1.19, P1.MP (MountPin), P2.1, P2.4, P2.7, P2.10, P2.13, P2.16, P2.19, P2.MP (MountPin), P3.1, P3.4, P3.7, P3.10, P3.13, P3.16, P3.19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
I2C_FARL_SCL: J1.40, P1.20, U1.22 (SCL), U10.13 (AP_SCL/AP_SCLK), U11.2 (SCL)
I2C_FARL_SDA: J1.39, P1.21, U1.23 (SDA), U10.14 (AP_SDA/AP_SDIO/AP_SDI), U11.1 (SDA)
I2C_FARR_SCL: J2.40, P3.20, U2.22 (SCL)
I2C_FARR_SDA: J2.39, P3.21, U2.23 (SDA)
I2C_NEARL_SCL: J1.42, P2.20
I2C_NEARL_SDA: J1.41, P2.21
I2C_NEARR_SCL: J2.42, P4.20
I2C_NEARR_SDA: J2.41, P4.21
IMU_AD0: R7.1, U10.1 (AP_SDO/AP_AD0)
IMU_FSYNC: R8.2, U10.9 (INT2/FSYNC/CLKIN)
IMU_INT1: R3.1, U1.15 (IO1_2), U10.4 (INT1)
IMU_INT1_SOM: J1.34, R3.2
LED_A: R4.1, U1.14 (IO1_1)
LED_A_ANODE: D1.2 (A), R4.2
LED_B: R5.1, U2.14 (IO1_1)
LED_B_ANODE: D2.2 (A), R5.2
LED_PWR_ANODE: D3.2 (A), R6.2
NEARL_3V3: C16.1, C17.1, P2.22, R51.1, U4.6 (VOUT)
NEARL_CK_N: J1.28, P2.8
NEARL_CK_P: J1.29, P2.9
NEARL_CT: C15.1, U4.4 (CT)
NEARL_D0_N: J1.25, P2.2
NEARL_D0_P: J1.26, P2.3
NEARL_D1_N: J1.23, P2.5
NEARL_D1_P: J1.24, P2.6
NEARL_DIR: U1.11 (IO0_7), U8.7 (DIR3), U8.8 (DIR4)
NEARL_IO0: P2.17, U1.9 (IO0_5)
NEARL_IO1: P2.18, U1.10 (IO0_6)
NEARL_PWR_EN: U1.8 (IO0_4), U4.3 (ON)
NEARL_QOD: R51.2, U4.5 (QOD)
NEARL_VIO: J5.4, R41.2
NEARL_XHS: J5.2, R17.2
NEARL_XHS_A: R16.1, U8.6 (A4)
NEARL_XHS_B: R17.1, U8.11 (B4)
NEARL_XVS: J5.1, R15.2
NEARL_XVS_A: R14.1, U8.5 (A3)
NEARL_XVS_B: R15.1, U8.12 (B3)
NEARR_3V3: C24.1, C25.1, P4.22, R53.1, U6.6 (VOUT)
NEARR_CK_N: J2.28, P4.8
NEARR_CK_P: J2.29, P4.9
NEARR_CT: C23.1, U6.4 (CT)
NEARR_D0_N: J2.25, P4.2
NEARR_D0_P: J2.26, P4.3
NEARR_D1_N: J2.23, P4.5
NEARR_D1_P: J2.24, P4.6
NEARR_DIR: U2.11 (IO0_7), U9.7 (DIR3), U9.8 (DIR4)
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
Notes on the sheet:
Sideline camera hub, rev A. Plugs into Antmicro's Jetson Orin Baseboard J7 (J1 here) and J8 (J2 here).
Baseboard stuffing for four 2-lane cameras: fit R122, remove R108 (CSI3 lanes to J8). Fit R4/R5 only if J2's GPIOs are wanted.
FFC: 50-pin 0.5 mm, pin N to pin N, as Antmicro's own camera boards use. Camera ports follow the Raspberry Pi 5 22-pin pinout.
Sync: SN74AVC4T774 DIR high = bus to head (slave), low = head to bus (master). PCA9555 pull-ups start every head powered,
enabled and isolated (OE high). Software sets one master (or none, with an external source on J3), then clears OE.
I2C (via the baseboard's mux): FAR-L bus has U1 PCA9555 0x20, U10 ICM-42688-P 0x69, U11 SHT45 0x44; FAR-R bus has U2 PCA9555 0x20.
